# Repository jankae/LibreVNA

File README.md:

# LibreVNA

**100kHz to 6GHz VNA**

This is the improved version of my [first attempt](https://www.github.com/jankae/VNA) at a VNA.

## GUI Installation

### Windows
* Download the latest [Release](https://github.com/jankae/LibreVNA/releases) and unpack the zip file
* Start the included LibreVNA-GUI.exe
* No installation or driver is required, simply move the extracted folder somewhere convenient

### Ubuntu
* Download the latest [Release](https://github.com/jankae/LibreVNA/releases) and unpack the zip file
* Install the required libraries:
```console
sudo apt install qt6-base-dev libqt6svg6
```
* Install the udev rule (otherwise you don't have the permissions to access the USB device):
```console
wget https://raw.githubusercontent.com/jankae/LibreVNA/master/Software/PC_Application/51-vna.rules
sudo cp 51-vna.rules /etc/udev/rules.d
```
* Either reboot or reload the udev rules manually:
```console
sudo udevadm control --reload-rules
sudo udevadm trigger
```
* You can now start GUI:
```console
cd $UNPACKED_ZIP_FOLDER$
./LibreVNA-GUI
```

### MacOS
* Download the latest [Release](https://github.com/jankae/LibreVNA/releases)
  * If you are using MacOS 14+ use the release with `latest` in the name.
  * If you are using MacOS >13.7 use the release with  `13.7` in the name.
* Unpack the zip file and move LibreVNA-GUI.app to your `/Applications` folder.
* Start LibreVNA-GUI.app and add a security exception to allow the Mac to run the app with an "untrusted" signing key.
* Launch app again.

## Quick Start
* You can find released versions of the GUI application and the device firmware [here](https://github.com/jankae/LibreVNA/releases).
* If you would like to try out the newest features, the compiled versions of each commit can be found [here](https://github.com/jankae/LibreVNA/actions) (but keep in mind that some features might be unstable or incomplete). If you are having trouble downloading them, please refer to this [guide](Documentation/DeveloperInfo/DownloadActionBuilds.md).
* An (incomplete) [user manual](Documentation/UserManual/manual.pdf) is also available.
* If you would like to control the LibreVNA with a script, see the [SCPI Programming Guide](Documentation/UserManual/ProgrammingGuide.pdf).

Please also take a look at the [FAQ](Documentation/FAQ.md).

If you notice bugs or have ideas for improvements, please create an issue for that.

For general questions or discussions, the [LibreVNA group](https://groups.io/g/LibreVNA-support/) is probably the best place.

### Preliminary specifications
Some [specifications](Documentation/UserManual/specsheet.pdf) are available but this project is still under development and the specifications might change.

There are also some initial [example measurements](Documentation/Measurements/Measurements.md).

## How does it work?
The PCB is really only the RF frontend with some processing power. Everything else is handled in the PC application once the data is transferred via USB. You can try out the application without the PCB (obviously no measurements are possible, but you can import provided example measurements and get an idea about what it can and can't do).
### RF path:

* The main clock source is an Si5351C, providing all the required clocks for the different blocks. It also serves as the stimulus source for frequencies below 25MHz. Its own reference clock is either a 26MHz crystal or an external 10MHz signal.
* The stimulus source for frequencies above 25MHz is a MAX2871. Its output signal is slightly filtered to reduce the amount of harmonics.
* The stimulus signal power can be adjusted between approximately -42 and -10dbm with a digital attenuator (RFSA3714).
* After the amplifier(TRF37A73) the signal is split and the weaker part of it fed into the reference receiver.
* The stronger part of the signal can be routed to either port. In each signal path, two RF switches are used in series to achieve higher isolation between the ports.
* Instead of directional couplers, resistive return-loss-bridges are used (easier to implement for wide bandwidth).
* Both ports have completely separated receive paths. This increases BOM cost but allows measuring two parameters at once (S11 and S21 or S22 and S12). It also avoids potential isolation issues that could arise if the receive paths would merge into a single mixer/ADC.
* Each receiver consists of two down-convert mixers. The 1.IF sits at 60MHz, the 2.IF 250kHz.
* The ADCs are sampling the final IF with 16bit@800kHz.

### Digital section:

* The central element is the Spartan6 FPGA. It handles all communication with the RF blocks and samples the ADCs. This allows for nearly instant switching of the measurement frequency, only limited by the settling time of the PLLs.
* The microcontroller handles the setup of the sweep in the FPGA, extracts and preprocesses the measurements and passes them on through USB.
* The flash contains the FPGA bitstream. Because the microcontroller has access to the flash, no FPGA-related hardware tools (such as JTAG programmers) are needed, everything can be updated via USB.

### Power supply:

* Everything is powered from USB (or optionally by external 5V DC)
* Almost every RF block has its own local regulater, preventing noise and signals coupling into the supply lines from propagating across the whole PCB

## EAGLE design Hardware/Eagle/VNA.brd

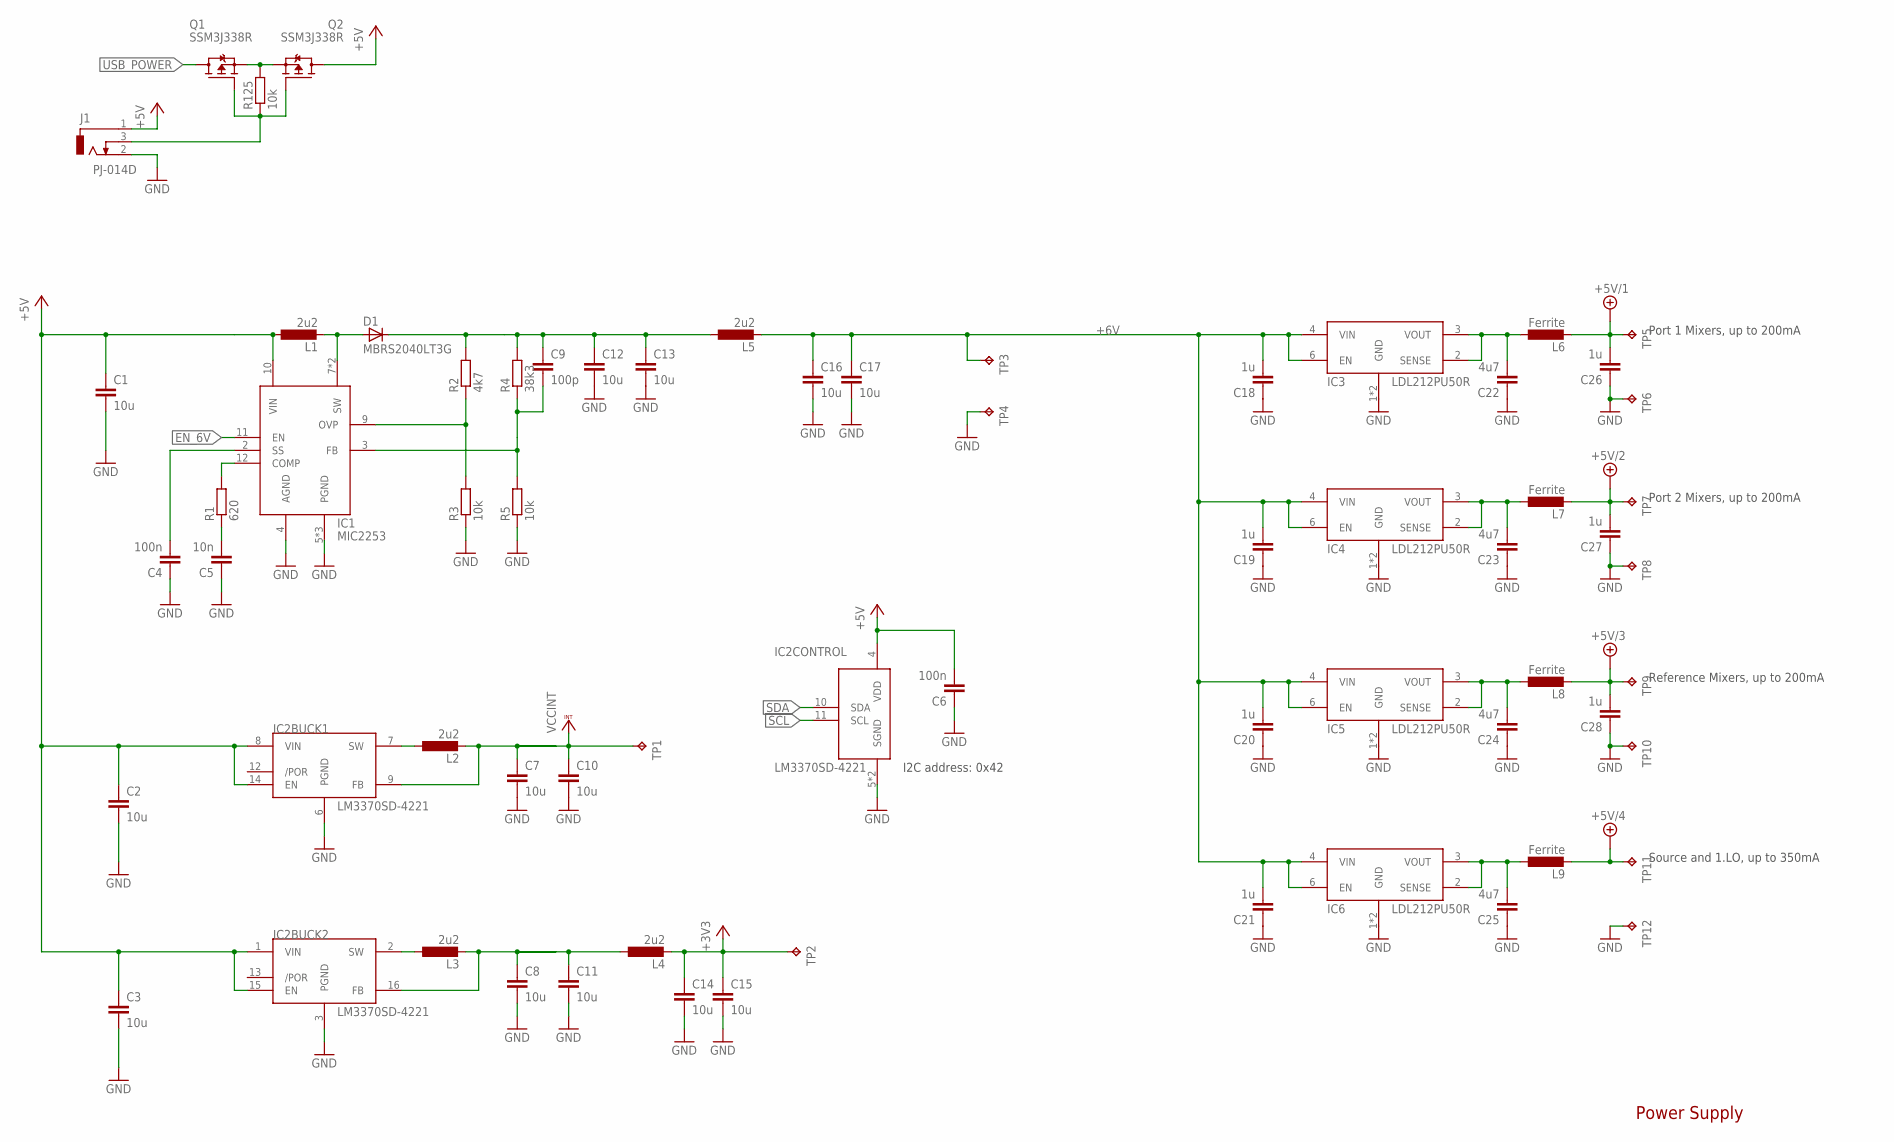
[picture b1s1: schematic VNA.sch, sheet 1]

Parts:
C1, C2, C3, C7, C8, C10, C11, C12, C13, C14, C15, C16, C17: 10u; C1206
C4, C6: 100n; C0402
C5: 10n; C0402
C9: 100p; C0402
C18, C19, C20, C21, C26, C27, C28: 1u; C0603
C22, C23, C24, C25: 4u7; C0603
D1: MBRS2040LT3G; SMB
IC1: MIC2253; SON50P300X300X90-13T170X240N
IC2: LM3370SD-4221; SON50P400X500X80-17T260X400N
IC3, IC4, IC5, IC6: LDL212PU50R; SON95P300X300X100-7T170X240N
J1: PJ-014D
L1, L2, L3, L4, L5: 2u2; SRN5040
L6, L7, L8, L9: Ferrite; R0402
Q1, Q2: SSM3J338R; SOTFL95P240X80-3N
R1: 620; R0402
R2: 4k7; R0402
R3, R5, R125: 10k; R0402
R4: 38k3; R0402
TP1, TP2, TP3, TP4, TP5, TP6, TP7, TP8, TP9, TP10, TP11, TP12: TPB1,27; B1,27

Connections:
+3V3: C14.1, C15.1, L4.P$2 (2), TP2.TP; also elsewhere on the board
+5V: C1.1, C2.1, C3.1, C6.2, IC1.10 (VIN), IC2.1 (VIN), IC2.4 (VDD), IC2.8 (VIN), IC2.14 (EN), IC2.15 (EN), J1.1, L1.P$1 (1), Q2.3 (D)
+5V/1: C26.2, L6.2, TP5.TP; also elsewhere on the board
+5V/2: C27.2, L7.2, TP7.TP; also elsewhere on the board
+5V/3: C28.2, L8.2, TP9.TP; also elsewhere on the board
+5V/4: L9.2, TP11.TP; also elsewhere on the board
+6V: C16.1, C17.1, C18.2, C19.2, C20.2, C21.2, IC3.4 (VIN), IC3.6 (EN), IC4.4 (VIN), IC4.6 (EN), IC5.4 (VIN), IC5.6 (EN), IC6.4 (VIN), IC6.6 (EN), L5.P$2 (2), TP3.TP
EN_6V: IC1.11 (EN); also elsewhere on the board
GND: C1.2, C2.2, C3.2, C4.1, C5.1, C6.1, C7.2, C8.2, C10.2, C11.2, C12.2, C13.2, C14.2, C15.2, C16.2, C17.2, C18.1, C19.1, C20.1, C21.1, C22.1, C23.1, C24.1, C25.1, C26.1, C27.1, C28.1, IC1.4 (AGND), IC1.5 (PGND), IC1.6 (PGND), IC1.13 (PGND), IC2.3 (PGND), IC2.5 (SGND), IC2.6 (PGND), IC2.17 (SGND), IC3.1 (GND), IC3.7 (GND), IC4.1 (GND), IC4.7 (GND), IC5.1 (GND), IC5.7 (GND), IC6.1 (GND), IC6.7 (GND), J1.2, R3.1, R5.1, TP4.TP, TP6.TP, TP8.TP, TP10.TP, TP12.TP; also elsewhere on the board
unnamed: D1.A, IC1.7 (SW), IC1.8 (SW), L1.P$2 (2)
unnamed: IC1.12 (COMP), R1.2
unnamed: C22.2, IC3.2 (SENSE), IC3.3 (VOUT), L6.1
unnamed: C9.2, IC1.3 (FB), R4.1, R5.2
unnamed: C23.2, IC4.2 (SENSE), IC4.3 (VOUT), L7.1
unnamed: IC1.9 (OVP), R2.1, R3.2
unnamed: C24.2, IC5.2 (SENSE), IC5.3 (VOUT), L8.1
unnamed: C4.2, IC1.2 (SS)
unnamed: C25.2, IC6.2 (SENSE), IC6.3 (VOUT), L9.1
unnamed: Q1.2 (S), Q2.2 (S), R125.2
unnamed: J1.3, Q1.1 (G), Q2.1 (G), R125.1
unnamed: IC2.7 (SW), L2.P$1 (1)
unnamed: C9.1, C12.1, C13.1, D1.C, L5.P$1 (1), R2.2, R4.2
unnamed: IC2.2 (SW), L3.P$1 (1)
unnamed: C8.1, C11.1, IC2.16 (FB), L3.P$2 (2), L4.P$1 (1)
unnamed: C5.2, R1.1
SCL: IC2.11 (SCL); also elsewhere on the board
SDA: IC2.10 (SDA); also elsewhere on the board
USB_POWER: Q1.3 (D); also elsewhere on the board
VCCINT: C7.1, C10.1, IC2.9 (FB), L2.P$2 (2), TP1.TP; also elsewhere on the board

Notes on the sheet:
Port 1 Mixers, up to 200mA
Port 2 Mixers, up to 200mA
Reference Mixers, up to 200mA
Source and 1.LO, up to 350mA
I2C address: 0x42
Power Supply

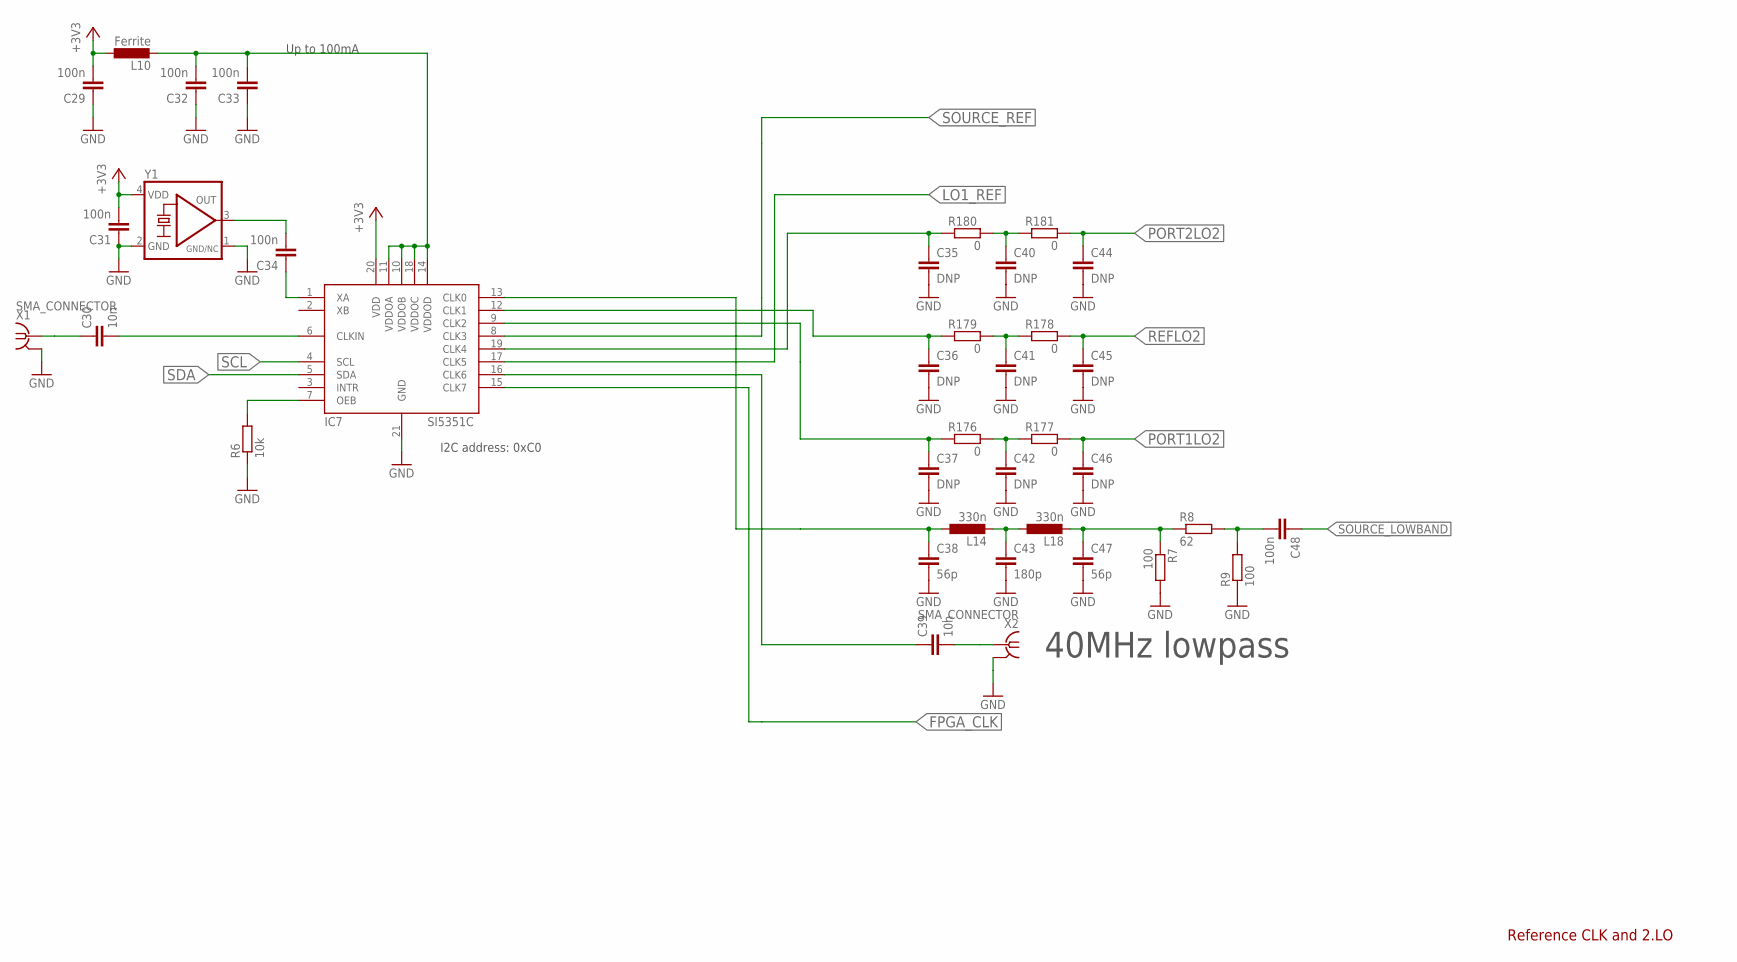
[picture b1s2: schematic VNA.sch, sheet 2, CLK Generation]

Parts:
C29, C31, C32, C33, C34, C48: 100n; C0402
C30, C39: 10n; C0402
C35, C36, C37, C40, C41, C42, C44, C45, C46: DNP; C0402
C38, C47: 56p; C0402
C43: 180p; C0402
IC7: SI5351C; QFN50P400X400X90-21T270N
L10: Ferrite; R0402
L14, L18: 330n; L0402
R6: 10k; R0402
R7, R9: 100; R0402
R8: 62; R0402
R176, R177, R178, R179, R180, R181: 0; R0402
X1, X2: SMA_CONNECTOR; J502-ND-142-0711-821/826
Y1: DSB221SDN/26MHz; 2.5X2.0_KXO-86-TCXO

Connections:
+3V3: C29.2, C31.2, IC7.20 (VDD), L10.1, Y1.4 (VDD); also elsewhere on the board
FPGA_CLK: IC7.15 (CLK7); also elsewhere on the board
GND: C29.1, C31.1, C32.1, C33.1, C35.2, C36.2, C37.2, C38.2, C40.2, C41.2, C42.2, C43.2, C44.2, C45.2, C46.2, C47.2, IC7.21 (GND), R6.1, R7.2, R9.1, X1.G@1 (2), X1.G@2 (2), X1.G@3 (2), X1.G@4 (2), X2.G@1 (2), X2.G@2 (2), X2.G@3 (2), X2.G@4 (2), Y1.1 (GND/NC), Y1.2 (GND); also elsewhere on the board
LO1_REF: IC7.17 (CLK5); also elsewhere on the board
unnamed: C43.1, L14.2, L18.1
unnamed: C39.2, X2.1
unnamed: C40.1, R180.2, R181.1
unnamed: C41.1, R178.1, R179.2
unnamed: C36.1, IC7.12 (CLK1), R179.1
unnamed: C42.1, R176.2, R177.1
unnamed: C35.1, IC7.19 (CLK4), R180.1
unnamed: C39.1, IC7.16 (CLK6)
unnamed: C30.1, X1.1
unnamed: C30.2, IC7.6 (CLKIN)
unnamed: C32.2, C33.2, IC7.10 (VDDOB), IC7.11 (VDDOA), IC7.14 (VDDOD), IC7.18 (VDDOC), L10.2
unnamed: IC7.7 (OEB), R6.2
unnamed: C34.2, Y1.3 (OUT)
unnamed: C34.1, IC7.1 (XA)
unnamed: C38.1, IC7.13 (CLK0), L14.1
unnamed: C48.2, R8.2, R9.2
unnamed: C37.1, IC7.9 (CLK2), R176.1
PORT1LO2: C46.1, R177.2; also elsewhere on the board
PORT2LO2: C44.1, R181.2; also elsewhere on the board
REFLO2: C45.1, R178.2; also elsewhere on the board
REFLO3: C47.1, L18.2, R7.1, R8.1
SCL: IC7.4 (SCL); also elsewhere on the board
SDA: IC7.5 (SDA); also elsewhere on the board
SOURCE_LOWBAND: C48.1; also elsewhere on the board
SOURCE_REF: IC7.8 (CLK3); also elsewhere on the board

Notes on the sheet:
Reference CLK and 2.LO
Up to 100mA
40MHz lowpass
I2C address: 0xC0

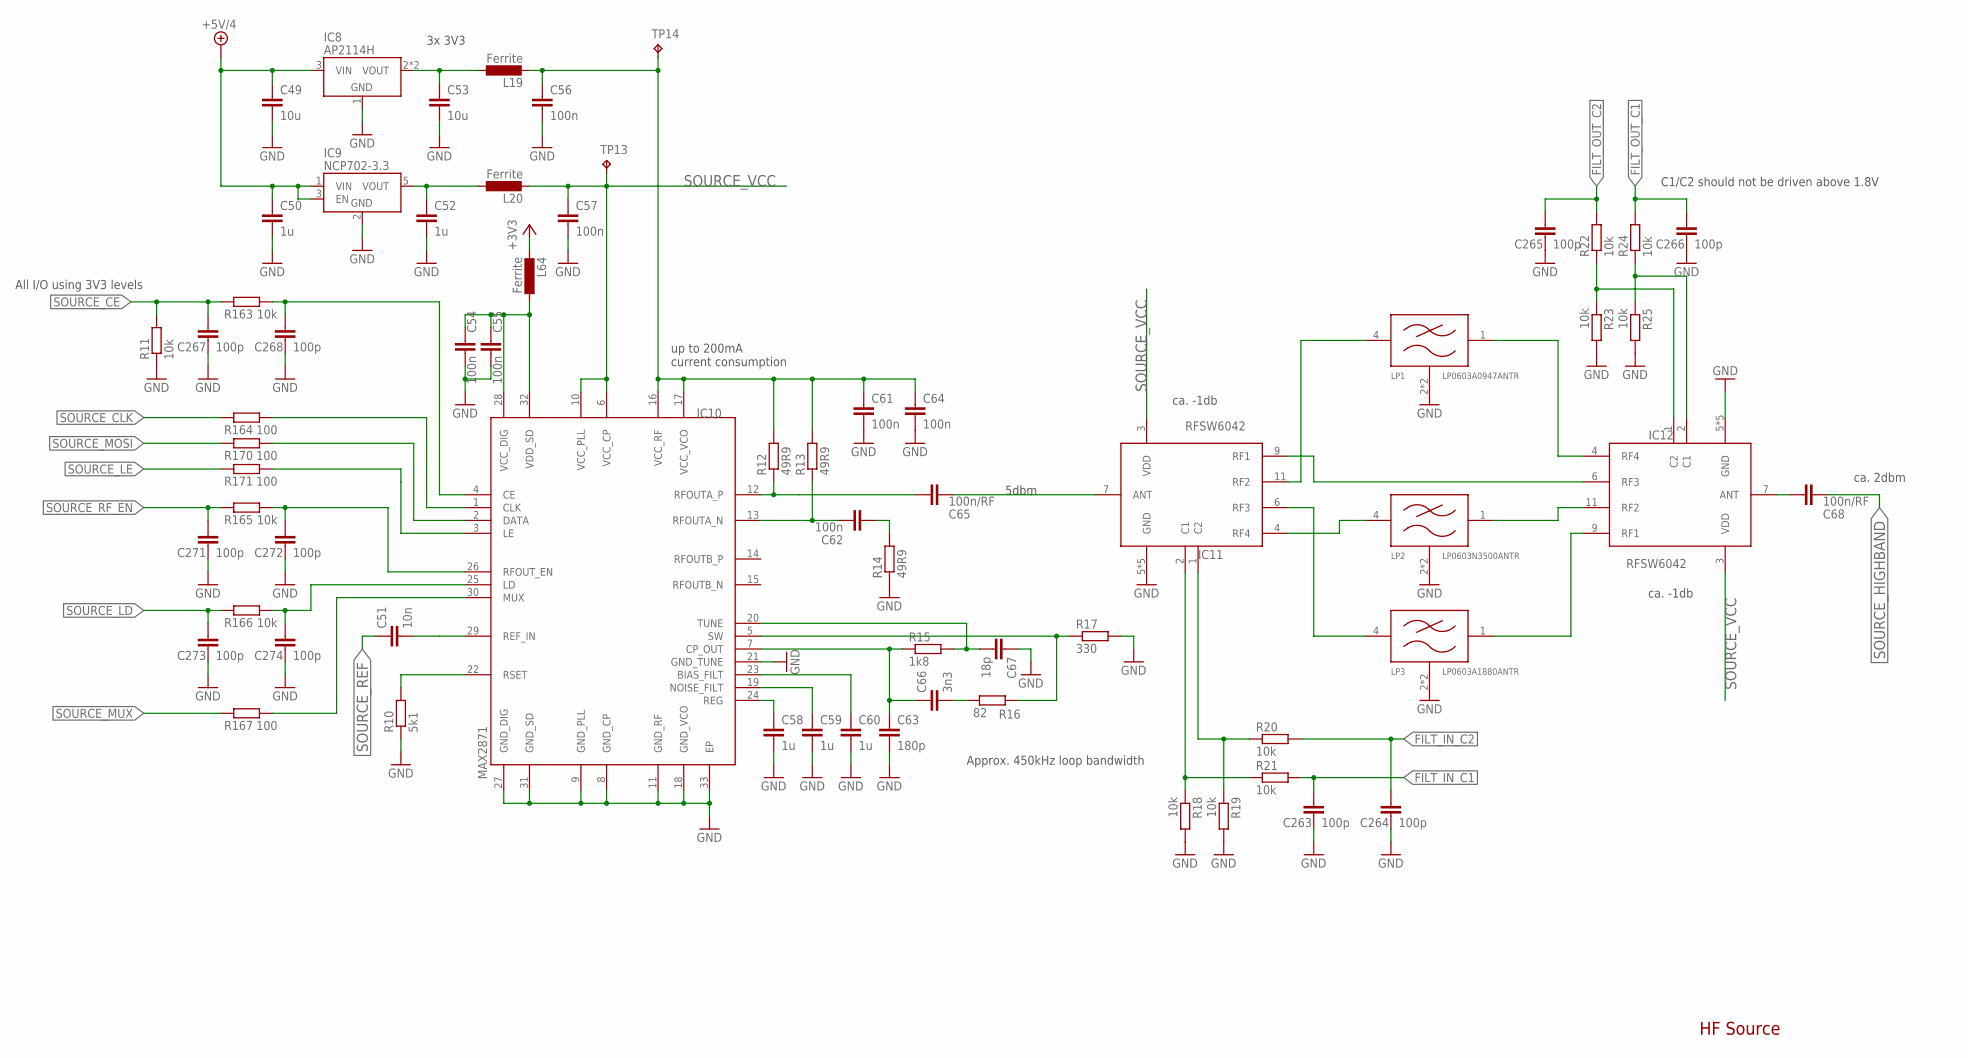
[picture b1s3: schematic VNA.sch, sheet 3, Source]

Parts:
C49, C53: 10u; C1206
C50, C52: 1u; C0603
C51: 10n; C0402
C54, C55, C56, C57, C61, C62, C64: 100n; C0402
C58, C59, C60: 1u; C0402
C63: 180p; C0402
C65, C68: 100n/RF; C0402
C66: 3n3; C0402
C67: 18p; C0402
C263, C264, C265, C266, C267, C268, C271, C272, C273, C274: 100p; C0402
IC8: AP2114H; SOT230P700X180-4
IC9: NCP702-3.3; SOT95P240X110-5
IC10: MAX2871; QFN50P500X500X80-33T310
IC11, IC12: RFSW6042; QFN40P180X180X55-13T76N
L19, L20, L64: Ferrite; R0402
LP1: LP0603A0947ANTR; FILTRDFN160X84X70-4N
LP2: LP0603N3500ANTR; FILTRDFN160X84X70-4N
LP3: LP0603A1880ANTR; FILTRDFN160X84X70-4N
R10: 5k1; R0402
R11, R18, R19, R20, R21, R22, R23, R24, R25, R163, R165, R166: 10k; R0402
R12, R13, R14: 49R9; R0402
R15: 1k8; R0402
R16: 82; R0402
R17: 330; R0402
R164, R167, R170, R171: 100; R0402
TP13, TP14: TPB1,27; B1,27

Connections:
+3V3: L64.2; also elsewhere on the board
+5V/4: C49.1, C50.1, IC8.3 (VIN), IC9.1 (VIN), IC9.3 (EN); also elsewhere on the board
FILT_IN_C1: C263.1, R21.2; also elsewhere on the board
FILT_IN_C2: C264.1, R20.2; also elsewhere on the board
FILT_OUT_C1: C266.1, R24.2; also elsewhere on the board
FILT_OUT_C2: C265.1, R22.2; also elsewhere on the board
GND: C49.2, C50.2, C52.2, C53.2, C54.2, C55.2, C56.2, C57.2, C58.2, C59.2, C60.2, C61.2, C63.2, C64.2, C67.1, C263.2, C264.2, C265.2, C266.2, C267.2, C268.2, C271.2, C272.2, C273.2, C274.2, IC8.1 (GND), IC9.2 (GND), IC10.8 (GND_CP), IC10.9 (GND_PLL), IC10.11 (GND_RF), IC10.18 (GND_VCO), IC10.21 (GND_TUNE), IC10.27 (GND_DIG), IC10.31 (GND_SD), IC10.33 (EP), IC11.5 (GND), IC11.8 (GND), IC11.10 (GND), IC11.12 (GND), IC11.13 (GND), IC12.5 (GND), IC12.8 (GND), IC12.10 (GND), IC12.12 (GND), IC12.13 (GND), LP1.2 (GND), LP1.3 (GND), LP2.2 (GND), LP2.3 (GND), LP3.2 (GND), LP3.3 (GND), R10.1, R11.1, R14.1, R17.2, R18.2, R19.2, R23.2, R25.2; also elsewhere on the board
unnamed: C67.2, IC10.20 (TUNE), R15.2
unnamed: C63.1, C66.1, IC10.7 (CP_OUT), R15.1
unnamed: C58.1, IC10.24 (REG)
unnamed: C59.1, IC10.19 (NOISE_FILT)
unnamed: C60.1, IC10.23 (BIAS_FILT)
unnamed: C66.2, R16.1
unnamed: IC10.5 (SW), R16.2, R17.1
unnamed: IC10.22 (RSET), R10.2
unnamed: C56.1, C61.1, C64.1, IC10.16 (VCC_RF), IC10.17 (VCC_VCO), L19.2, R12.2, R13.2, TP14.TP
unnamed: C51.2, IC10.29 (REF_IN)
unnamed: C65.1, IC10.12 (RFOUTA_P), R12.1
unnamed: C62.2, IC10.13 (RFOUTA_N), R13.1
unnamed: C62.1, R14.2
unnamed: C65.2, IC11.7 (ANT)
unnamed: IC11.9 (RF1), IC12.6 (RF3)
unnamed: IC11.11 (RF2), LP1.4 (IN)
unnamed: IC12.4 (RF4), LP1.1 (OUT)
unnamed: IC12.11 (RF2), LP2.1 (OUT)
unnamed: IC12.9 (RF1), LP3.1 (OUT)
unnamed: IC11.6 (RF3), LP3.4 (IN)
unnamed: IC11.4 (RF4), LP2.4 (IN)
unnamed: C53.1, IC8.2 (VOUT), IC8.4 (VOUT), L19.1
unnamed: C52.1, IC9.5 (VOUT), L20.1
unnamed: C68.1, IC12.7 (ANT)
unnamed: C268.1, IC10.4 (CE), R163.1
unnamed: IC11.2 (C1), R18.1, R21.1
unnamed: IC11.1 (C2), R19.1, R20.1
unnamed: IC12.1 (C2), R22.1, R23.1
unnamed: IC12.2 (C1), R24.1, R25.1
unnamed: IC10.1 (CLK), R164.1
unnamed: IC10.2 (DATA), R170.1
unnamed: IC10.3 (LE), R171.1
unnamed: IC10.30 (MUX), R167.1
unnamed: C272.1, IC10.26 (RFOUT_EN), R165.1
unnamed: C274.1, IC10.25 (LD), R166.1
unnamed: C54.1, C55.1, IC10.28 (VCC_DIG), IC10.32 (VDD_SD), L64.1
SOURCE_CE: C267.1, R11.2, R163.2; also elsewhere on the board
SOURCE_CLK: R164.2; also elsewhere on the board
SOURCE_HIGHBAND: C68.2; also elsewhere on the board
SOURCE_LD: C273.1, R166.2; also elsewhere on the board
SOURCE_LE: R171.2; also elsewhere on the board
SOURCE_MOSI: R170.2; also elsewhere on the board
SOURCE_MUX: R167.2; also elsewhere on the board
SOURCE_REF: C51.1; also elsewhere on the board
SOURCE_RF_EN: C271.1, R165.2; also elsewhere on the board
SOURCE_VCC: C57.1, IC10.6 (VCC_CP), IC10.10 (VCC_PLL), IC11.3 (VDD), IC12.3 (VDD), L20.2, TP13.TP

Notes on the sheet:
up to 200mA current consumption
All I/O using 3V3 levels
3x 3V3
Approx. 450kHz loop bandwidth
5dbm
ca. -1db
ca. 2dbm
C1/C2 should not be driven above 1.8V
HF Source

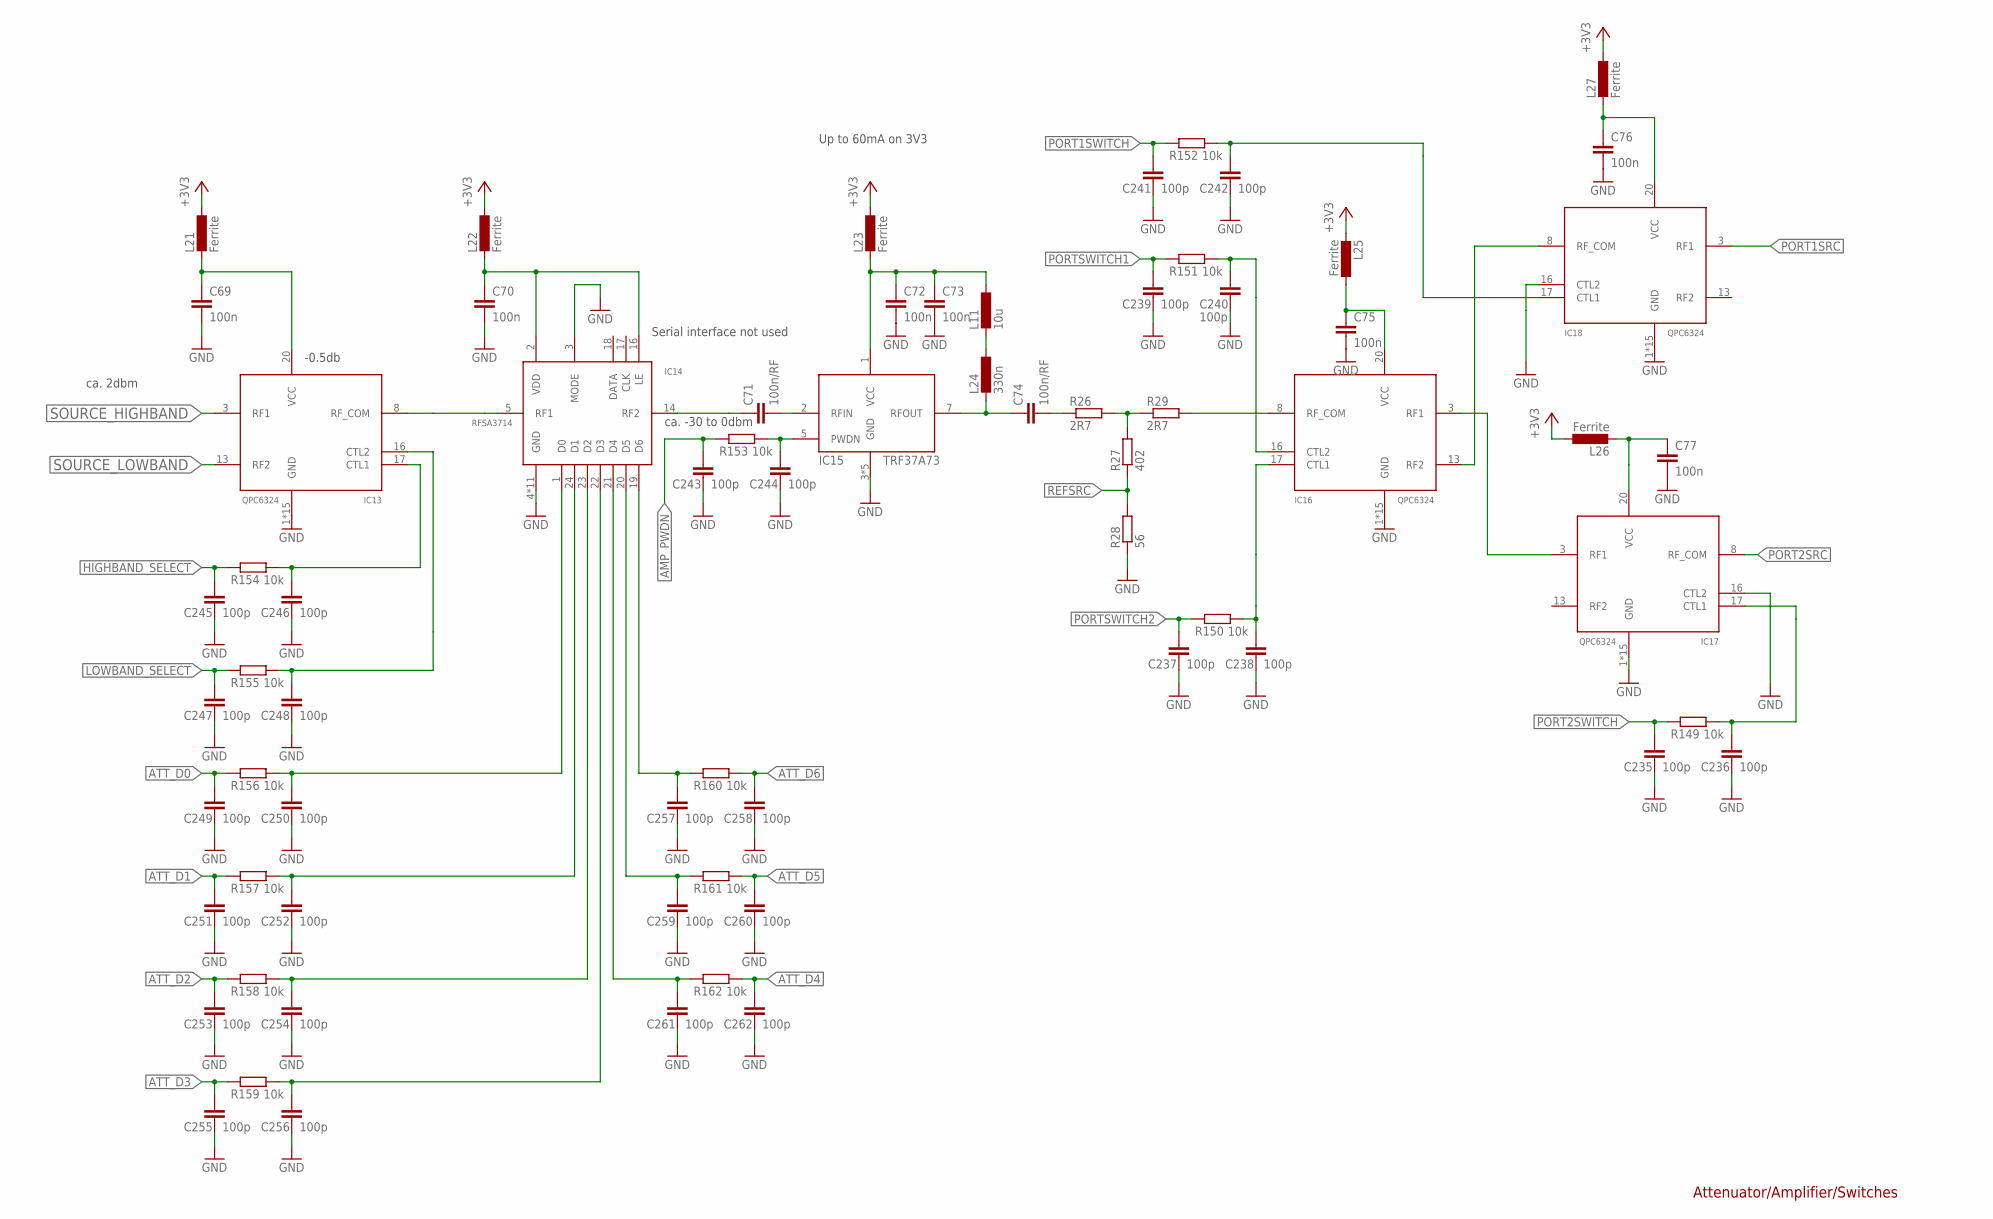
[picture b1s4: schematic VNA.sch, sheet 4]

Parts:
C69, C70, C72, C73, C75, C76, C77: 100n; C0402
C71, C74: 100n/RF; C0402
C235, C236, C237, C238, C239, C240, C241, C242, C243, C244, C245, C246, C247, C248, C249, C250, C251, C252, C253, C254, C255, C256, C257, C258, C259, C260, C261, C262: 100p; C0402
IC13, IC16, IC17, IC18: QPC6324; QFN50P400X400X75-21T206
IC14: RFSA3714; QFN50P400X400X75-25T270
IC15: TRF37A73; SON50P200X200X80-9T90X160N
L11: 10u; INDC2012X100N
L21, L22, L23, L25, L26, L27: Ferrite; R0402
L24: 330n; L0402
R26, R29: 2R7; R0402
R27: 402; R0402
R28: 56; R0402
R149, R150, R151, R152, R153, R154, R155, R156, R157, R158, R159, R160, R161, R162: 10k; R0402

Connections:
+3V3: L21.1, L22.1, L23.1, L25.2, L26.1, L27.1; also elsewhere on the board
AMP_PWDN: C243.1, R153.2; also elsewhere on the board
ATT_D0: C249.1, R156.2; also elsewhere on the board
ATT_D1: C251.1, R157.2; also elsewhere on the board
ATT_D2: C253.1, R158.2; also elsewhere on the board
ATT_D3: C255.1, R159.2; also elsewhere on the board
ATT_D4: C262.1, R162.1; also elsewhere on the board
ATT_D5: C260.1, R161.1; also elsewhere on the board
ATT_D6: C258.1, R160.1; also elsewhere on the board
GND: C69.2, C70.2, C72.2, C73.2, C75.2, C76.2, C77.2, C235.2, C236.2, C237.2, C238.2, C239.2, C240.2, C241.2, C242.2, C243.2, C244.2, C245.2, C246.2, C247.2, C248.2, C249.2, C250.2, C251.2, C252.2, C253.2, C254.2, C255.2, C256.2, C257.2, C258.2, C259.2, C260.2, C261.2, C262.2, IC13.1 (GND), IC13.2 (GND), IC13.4 (GND), IC13.5 (GND), IC13.6 (GND), IC13.7 (GND), IC13.9 (GND), IC13.10 (GND), IC13.11 (GND), IC13.12 (GND), IC13.14 (GND), IC13.15 (GND), IC13.18 (GND), IC13.19 (GND), IC13.21 (GND), IC14.3 (MODE), IC14.4 (GND), IC14.6 (GND), IC14.7 (GND), IC14.8 (GND), IC14.9 (GND), IC14.10 (GND), IC14.11 (GND), IC14.12 (GND), IC14.13 (GND), IC14.15 (GND), IC14.25 (GND), IC15.3 (GND), IC15.4 (GND), IC15.6 (GND), IC15.8 (GND), IC15.9 (GND), IC16.1 (GND), IC16.2 (GND), IC16.4 (GND), IC16.5 (GND), IC16.6 (GND), IC16.7 (GND), IC16.9 (GND), IC16.10 (GND), IC16.11 (GND), IC16.12 (GND), IC16.14 (GND), IC16.15 (GND), IC16.18 (GND), IC16.19 (GND), IC16.21 (GND), IC17.1 (GND), IC17.2 (GND), IC17.4 (GND), IC17.5 (GND), IC17.6 (GND), IC17.7 (GND), IC17.9 (GND), IC17.10 (GND), IC17.11 (GND), IC17.12 (GND), IC17.14 (GND), IC17.15 (GND), IC17.16 (CTL2), IC17.18 (GND), IC17.19 (GND), IC17.21 (GND), IC18.1 (GND), IC18.2 (GND), IC18.4 (GND), IC18.5 (GND), IC18.6 (GND), IC18.7 (GND), IC18.9 (GND), IC18.10 (GND), IC18.11 (GND), IC18.12 (GND), IC18.14 (GND), IC18.15 (GND), IC18.16 (CTL2), IC18.18 (GND), IC18.19 (GND), IC18.21 (GND), R28.1; also elsewhere on the board
HIGHBAND_SELECT: C245.1, R154.2; also elsewhere on the board
LOWBAND_SELECT: C247.1, R155.2; also elsewhere on the board
unnamed: C77.1, IC17.20 (VCC), L26.2
unnamed: C69.1, IC13.20 (VCC), L21.2
unnamed: IC13.8 (RF_COM), IC14.5 (RF1)
unnamed: C70.1, IC14.2 (VDD), IC14.16 (LE), L22.2
unnamed: C71.1, IC14.14 (RF2)
unnamed: C71.2, IC15.2 (RFIN)
unnamed: C74.1, IC15.7 (RFOUT), L24.2
unnamed: C74.2, R26.1
unnamed: IC16.8 (RF_COM), R29.2
unnamed: C72.1, C73.1, IC15.1 (VCC), L11.1, L23.2
unnamed: R26.2, R27.2, R29.1
unnamed: IC16.13 (RF2), IC18.8 (RF_COM)
unnamed: IC16.3 (RF1), IC17.3 (RF1)
unnamed: C76.1, IC18.20 (VCC), L27.2
unnamed: C236.1, IC17.17 (CTL1), R149.1
unnamed: C240.1, IC16.16 (CTL2), R151.1
unnamed: C238.1, IC16.17 (CTL1), R150.1
unnamed: C242.1, IC18.17 (CTL1), R152.1
unnamed: C244.1, IC15.5 (PWDN), R153.1
unnamed: C246.1, IC13.17 (CTL1), R154.1
unnamed: C250.1, IC14.1 (D0), R156.1
unnamed: C248.1, IC13.16 (CTL2), R155.1
unnamed: C252.1, IC14.24 (D1), R157.1
unnamed: C75.1, IC16.20 (VCC), L25.1
unnamed: C254.1, IC14.23 (D2), R158.1
unnamed: C256.1, IC14.22 (D3), R159.1
unnamed: C257.1, IC14.19 (D6), R160.2
unnamed: C259.1, IC14.20 (D5), R161.2
unnamed: C261.1, IC14.21 (D4), R162.2
unnamed: L11.2, L24.1
PORT1SRC: IC18.3 (RF1); also elsewhere on the board
PORT1SWITCH: C241.1, R152.2; also elsewhere on the board
PORT2SRC: IC17.8 (RF_COM); also elsewhere on the board
PORT2SWITCH: C235.1, R149.2; also elsewhere on the board
PORTSWITCH1: C239.1, R151.2; also elsewhere on the board
PORTSWITCH2: C237.1, R150.2; also elsewhere on the board
REFSRC: R27.1, R28.2; also elsewhere on the board
SOURCE_HIGHBAND: IC13.3 (RF1); also elsewhere on the board
SOURCE_LOWBAND: IC13.13 (RF2); also elsewhere on the board

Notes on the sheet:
Serial interface not used
ca. 2dbm
-0.5db
ca. -30 to 0dbm
Up to 60mA on 3V3
Attenuator/Amplifier/Switches

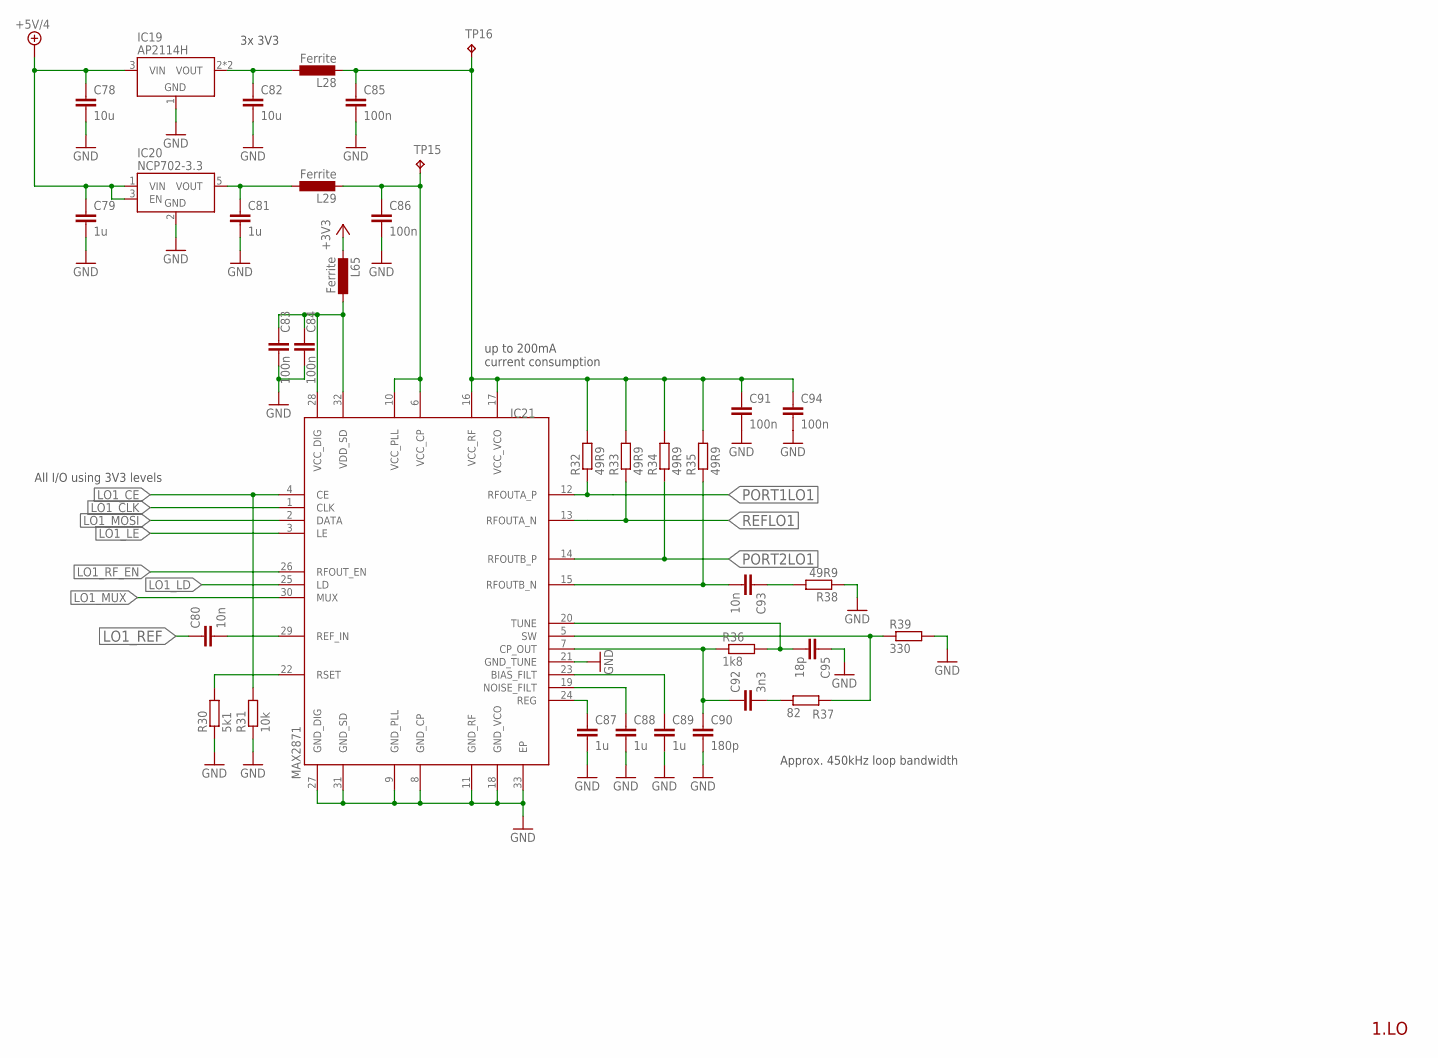
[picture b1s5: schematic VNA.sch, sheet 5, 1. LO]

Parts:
C78, C82: 10u; C1206
C79, C81: 1u; C0603
C80, C93: 10n; C0402
C83, C84, C85, C86, C91, C94: 100n; C0402
C87, C88, C89: 1u; C0402
C90: 180p; C0402
C92: 3n3; C0402
C95: 18p; C0402
IC19: AP2114H; SOT230P700X180-4
IC20: NCP702-3.3; SOT95P240X110-5
IC21: MAX2871; QFN50P500X500X80-33T310
L28, L29, L65: Ferrite; R0402
R30: 5k1; R0402
R31: 10k; R0402
R32, R33, R34, R35, R38: 49R9; R0402
R36: 1k8; R0402
R37: 82; R0402
R39: 330; R0402
TP15, TP16: TPB1,27; B1,27

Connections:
+3V3: L65.2; also elsewhere on the board
+5V/4: C78.1, C79.1, IC19.3 (VIN), IC20.1 (VIN), IC20.3 (EN); also elsewhere on the board
GND: C78.2, C79.2, C81.2, C82.2, C83.2, C84.2, C85.2, C86.2, C87.2, C88.2, C89.2, C90.2, C91.2, C94.2, C95.1, IC19.1 (GND), IC20.2 (GND), IC21.8 (GND_CP), IC21.9 (GND_PLL), IC21.11 (GND_RF), IC21.18 (GND_VCO), IC21.21 (GND_TUNE), IC21.27 (GND_DIG), IC21.31 (GND_SD), IC21.33 (EP), R30.1, R31.1, R38.1, R39.2; also elsewhere on the board
LO1_CE: IC21.4 (CE), R31.2; also elsewhere on the board
LO1_CLK: IC21.1 (CLK); also elsewhere on the board
LO1_LD: IC21.25 (LD); also elsewhere on the board
LO1_LE: IC21.3 (LE); also elsewhere on the board
LO1_MOSI: IC21.2 (DATA); also elsewhere on the board
LO1_MUX: IC21.30 (MUX); also elsewhere on the board
LO1_REF: C80.1; also elsewhere on the board
LO1_RF_EN: IC21.26 (RFOUT_EN); also elsewhere on the board
unnamed: C86.1, IC21.6 (VCC_CP), IC21.10 (VCC_PLL), L29.2, TP15.TP
unnamed: C95.2, IC21.20 (TUNE), R36.2
unnamed: C90.1, C92.1, IC21.7 (CP_OUT), R36.1
unnamed: C87.1, IC21.24 (REG)
unnamed: C88.1, IC21.19 (NOISE_FILT)
unnamed: C89.1, IC21.23 (BIAS_FILT)
unnamed: C92.2, R37.1
unnamed: IC21.5 (SW), R37.2, R39.1
unnamed: IC21.22 (RSET), R30.2
unnamed: C85.1, C91.1, C94.1, IC21.16 (VCC_RF), IC21.17 (VCC_VCO), L28.2, R32.2, R33.2, R34.2, R35.2, TP16.TP
unnamed: C80.2, IC21.29 (REF_IN)
unnamed: C93.1, R38.2
unnamed: C82.1, IC19.2 (VOUT), IC19.4 (VOUT), L28.1
unnamed: C81.1, IC20.5 (VOUT), L29.1
unnamed: C93.2, IC21.15 (RFOUTB_N), R35.1
unnamed: C83.1, C84.1, IC21.28 (VCC_DIG), IC21.32 (VDD_SD), L65.1
PORT1LO1: IC21.12 (RFOUTA_P), R32.1; also elsewhere on the board
PORT2LO1: IC21.14 (RFOUTB_P), R34.1; also elsewhere on the board
REFLO1: IC21.13 (RFOUTA_N), R33.1; also elsewhere on the board

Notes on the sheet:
up to 200mA current consumption
All I/O using 3V3 levels
3x 3V3
Approx. 450kHz loop bandwidth
1.LO

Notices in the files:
parts and their libraries:
crystal-geyer_V1_0: Copyright: Geyer-Electronic
